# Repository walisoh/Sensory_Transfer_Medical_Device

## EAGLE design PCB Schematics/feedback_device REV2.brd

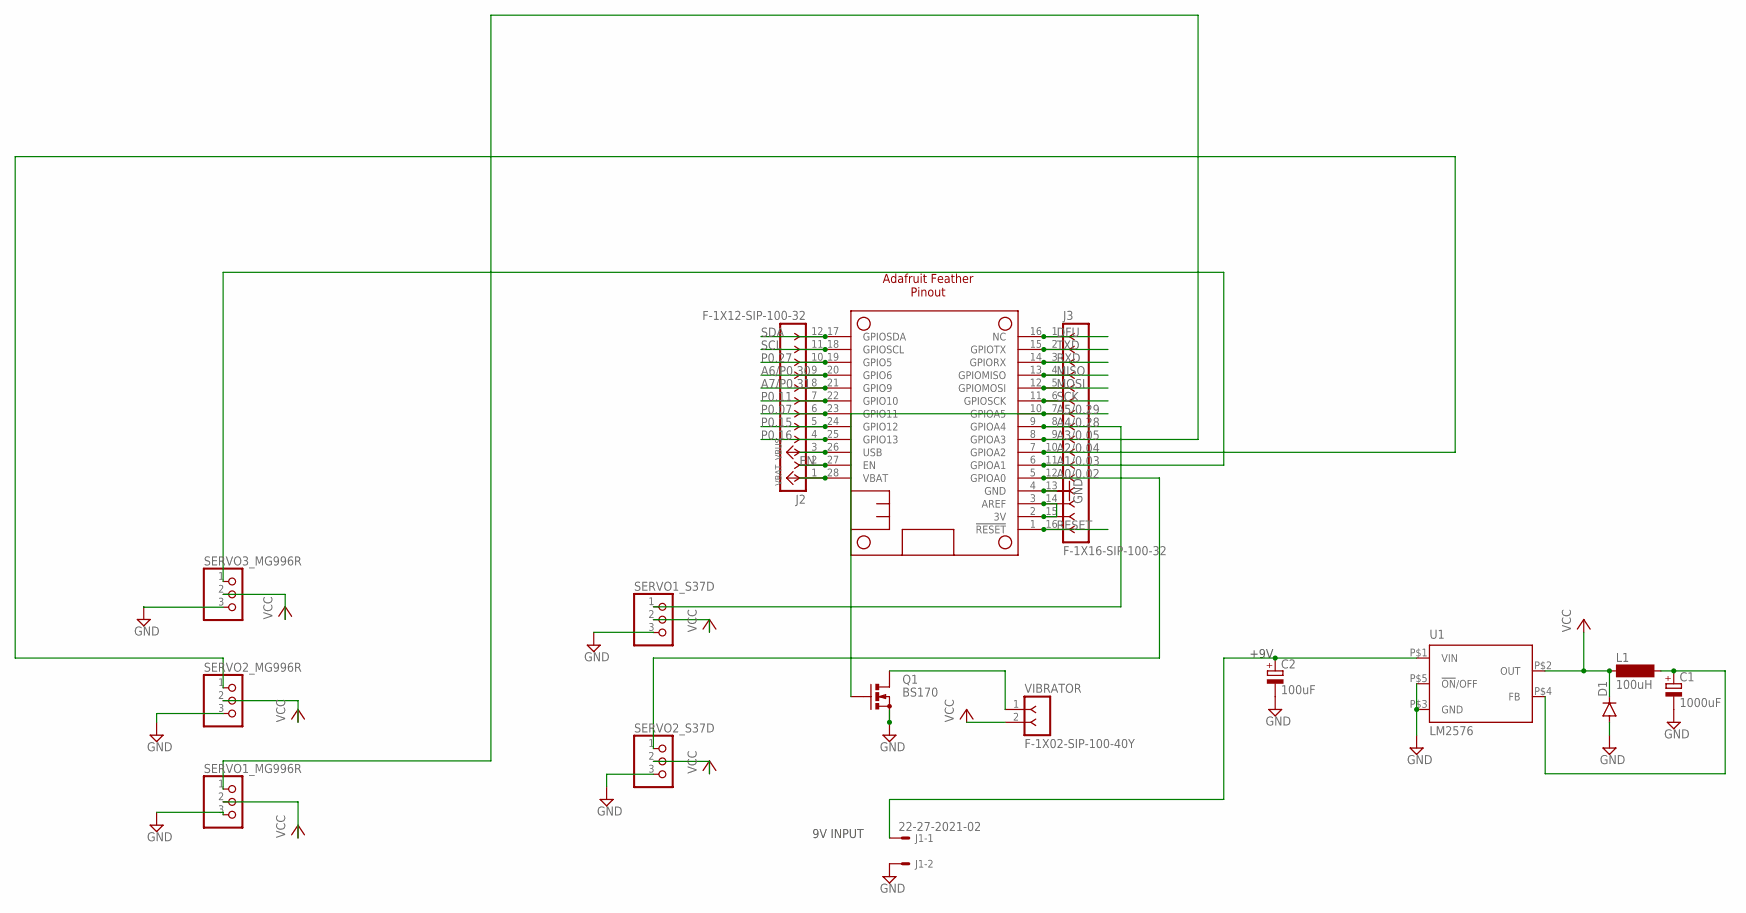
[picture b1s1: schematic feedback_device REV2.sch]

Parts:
C1: 1000uF; E5-8,5
C2: 100uF; E2,5-7
D1: DIODE-SMB; SMB
J1: 22-27-2021-02; 6410-02
J2: F-1X12-SIP-100-32; SIP-100-12-32
J3: F-1X16-SIP-100-32; SIP-100-16-32
L1: 100uH; SD75
MS1: FEATHERWING_NODIM
Q1: BS170; SOT54E
SERVO1_MG996R, SERVO1_S37D, SERVO2_MG996R, SERVO2_S37D, SERVO3_MG996R: PINHD-1X3; 1X03
U1: LM2576
VIBRATOR: F-1X02-SIP-100-40Y; SIP-100-02-40Y

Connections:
3V: J3.14, J3.15, MS1.2 (3V), MS1.3 (AREF)
A0/0.02: J3.12, MS1.5 (GPIOA0), SERVO2_S37D.1
A1/0.03: J3.11, MS1.6 (GPIOA1), SERVO3_MG996R.1
A2/0.04: J3.10, MS1.7 (GPIOA2), SERVO2_MG996R.1
A3/0.05: J3.9, MS1.8 (GPIOA3), SERVO1_MG996R.1
A4/0.28: J3.8, MS1.9 (GPIOA4), SERVO1_S37D.1
A5/0.29: J3.7, MS1.10 (GPIOA5), Q1.G
A6/P0.30: J2.9, MS1.20 (GPIO6)
A7/P0.31: J2.8, MS1.21 (GPIO9)
DFU: J3.1, MS1.16 (NC)
EN: J2.2, MS1.27 (EN)
GND: C1.-, C2.-, D1.A, J1.2, J3.13, MS1.4 (GND), Q1.S, SERVO1_MG996R.3, SERVO1_S37D.3, SERVO2_MG996R.3, SERVO2_S37D.3, SERVO3_MG996R.3, U1.P$3 (GND), U1.P$5 (!ON!/OFF)
MISO: J3.4, MS1.13 (GPIOMISO)
MOSI: J3.5, MS1.12 (GPIOMOSI)
unnamed: Q1.D, VIBRATOR.1
unnamed: C2.+, J1.1, U1.P$1 (VIN)
unnamed: C1.+, L1.2, U1.P$4 (FB)
P0.07: J2.6, MS1.23 (GPIO11)
P0.11: J2.7, MS1.22 (GPIO10)
P0.15: J2.5, MS1.24 (GPIO12)
P0.16: J2.4, MS1.25 (GPIO13)
P0.27: J2.10, MS1.19 (GPIO5)
RESET: J3.16, MS1.1 (!RESET)
RXD: J3.3, MS1.14 (GPIORX)
SCK: J3.6, MS1.11 (GPIOSCK)
SCL: J2.11, MS1.18 (GPIOSCL)
SDA: J2.12, MS1.17 (GPIOSDA)
TXD: J3.2, MS1.15 (GPIOTX)
VBAT: J2.1, MS1.28 (VBAT)
VBUS: J2.3, MS1.26 (USB)
VCC: D1.C, L1.1, SERVO1_MG996R.2, SERVO1_S37D.2, SERVO2_MG996R.2, SERVO2_S37D.2, SERVO3_MG996R.2, U1.P$2 (OUT), VIBRATOR.2

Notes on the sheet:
Adafruit Feather Pinout
+9V
9V INPUT

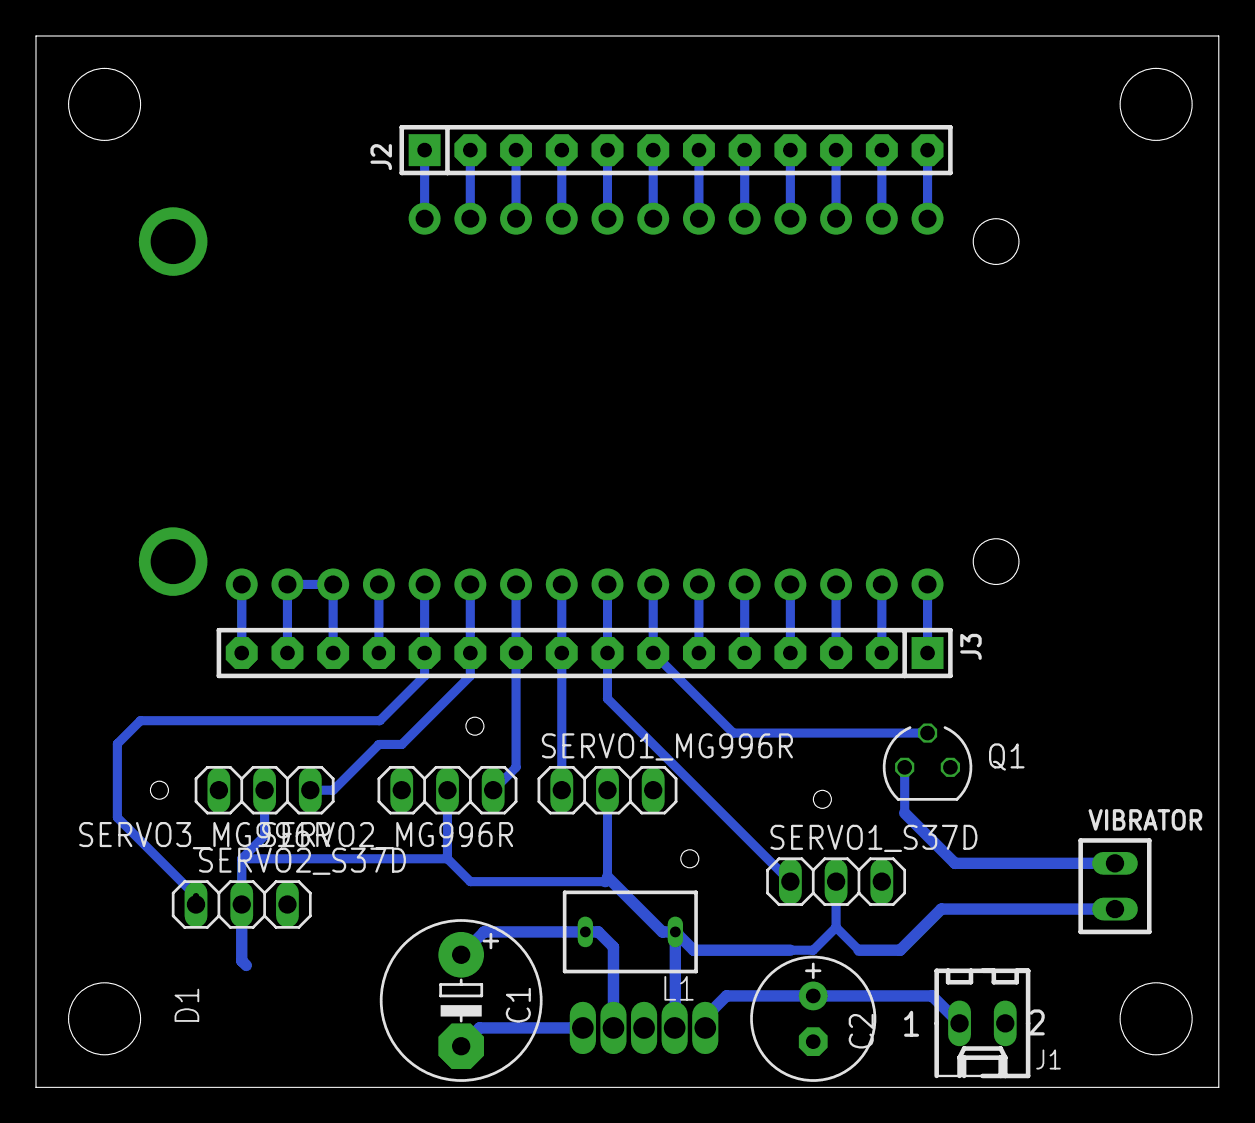
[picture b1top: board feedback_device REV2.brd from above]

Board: 2 copper layers, 65.7 x 58.4 mm, 16 parts (1 on the bottom side), 31 nets.

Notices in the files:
parts and their libraries:
microbuilder: This work is placed in the public domain, and may be freely used for commercial and non-commercial work with the following conditions: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
con-headers-jp: Copyright (C) 2008, Bob Starr
